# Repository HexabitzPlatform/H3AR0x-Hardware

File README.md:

# H3AR0x-Hardware
Hexabitz Module DIP Adapter Hardware Design

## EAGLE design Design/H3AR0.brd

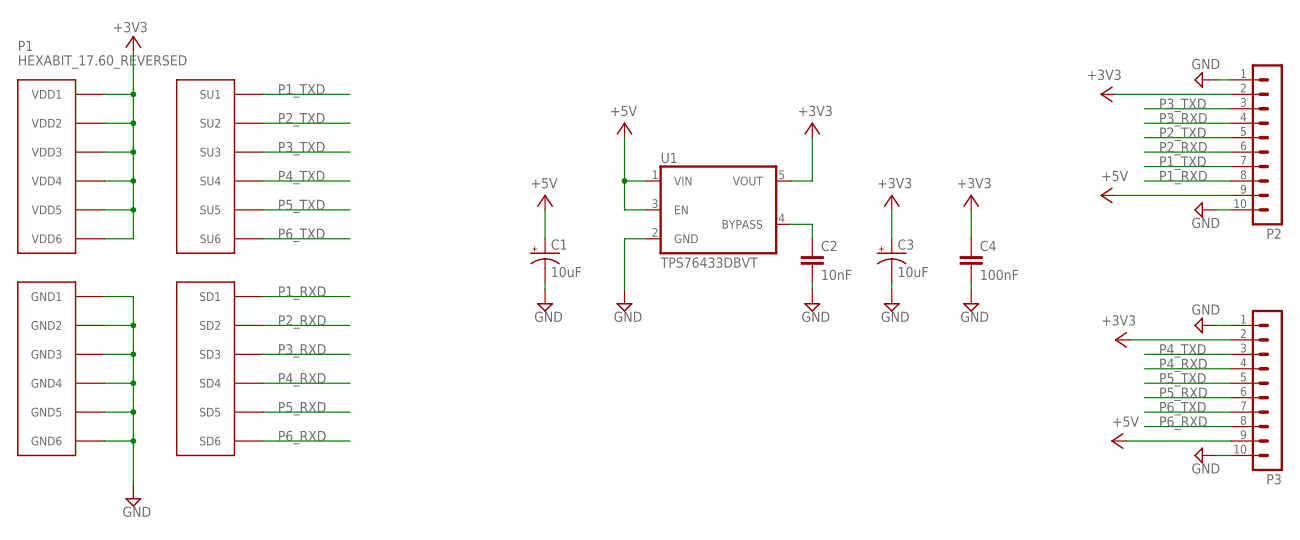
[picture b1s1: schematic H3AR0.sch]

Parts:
C1, C3: 10uF; C-1210-POL; MPN TPSB106K016R0500
C2: 10nF; C-0603; TOLERANCE 10%; VOLTAGE_RATING 50V; MPN C0603C103K5RACTU
C4: 100nF; C-0603; TOLERANCE 10%; VOLTAGE_RATING 10V; MPN C0603C104K8RACTU
P1: HEXABIT_17.60_REVERSED
P2, P3: MA10-1; MPN 61301011121
TRIMBLE-LOGO1: HEXA-LOGO
U1: TPS76433DBVT; SOT25

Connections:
+3V3: C3.1 (+), C4.1, P1.PAD_PU7 (VDD1), P1.PAD_PU8 (VDD2), P1.PAD_PU9 (VDD3), P1.PAD_PU10 (VDD4), P1.PAD_PU11 (VDD5), P1.PAD_PU12 (VDD6), P2.2, P3.2, U1.5 (VOUT)
+5V: C1.1 (+), P2.9, P3.9, U1.1 (VIN), U1.3 (EN)
GND: C1.2 (-), C2.2, C3.2 (-), C4.2, P1.PAD_PD7 (GND1), P1.PAD_PD8 (GND2), P1.PAD_PD9 (GND3), P1.PAD_PD10 (GND4), P1.PAD_PD11 (GND5), P1.PAD_PD12 (GND6), P2.1, P2.10, P3.1, P3.10, U1.2 (GND)
unnamed: C2.1, U1.4 (BYPASS)
P1_RXD: P1.PAD_PD1 (SD1), P2.8
P1_TXD: P1.PAD_PU1 (SU1), P2.7
P2_RXD: P1.PAD_PD2 (SD2), P2.6
P2_TXD: P1.PAD_PU2 (SU2), P2.5
P3_RXD: P1.PAD_PD3 (SD3), P2.4
P3_TXD: P1.PAD_PU3 (SU3), P2.3
P4_RXD: P1.PAD_PD4 (SD4), P3.4
P4_TXD: P1.PAD_PU4 (SU4), P3.3
P5_RXD: P1.PAD_PD5 (SD5), P3.6
P5_TXD: P1.PAD_PU5 (SU5), P3.5
P6_RXD: P1.PAD_PD6 (SD6), P3.8
P6_TXD: P1.PAD_PU6 (SU6), P3.7

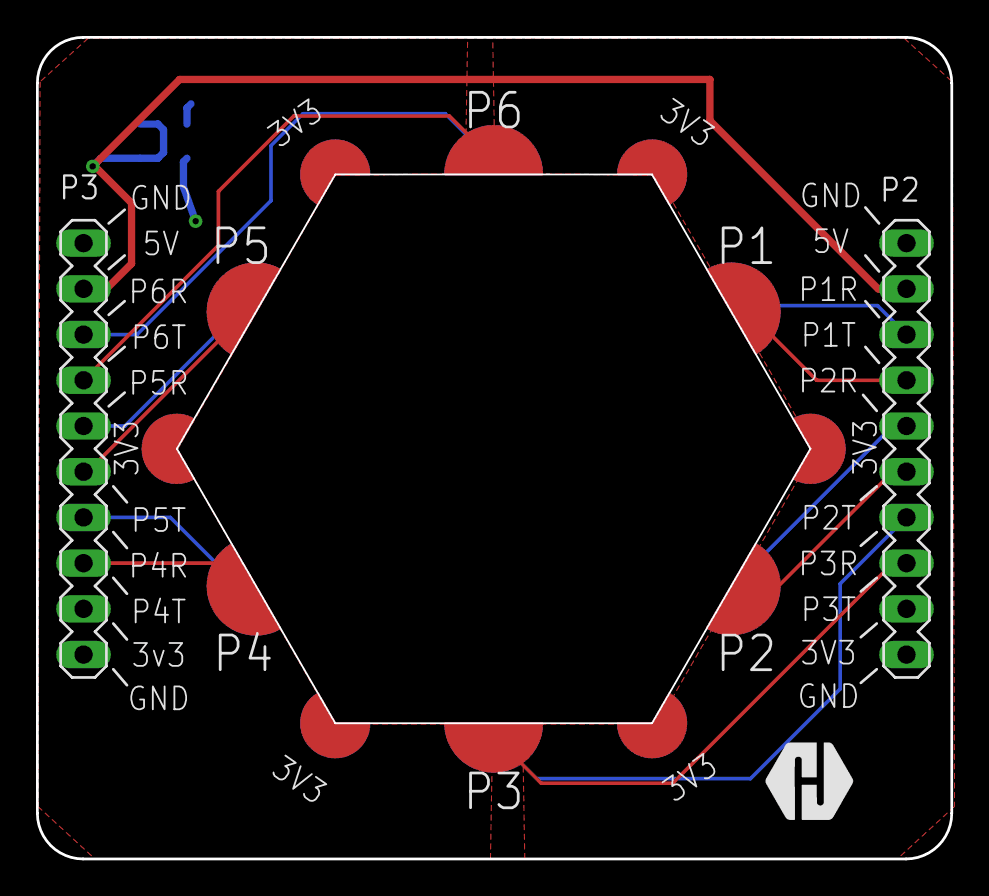
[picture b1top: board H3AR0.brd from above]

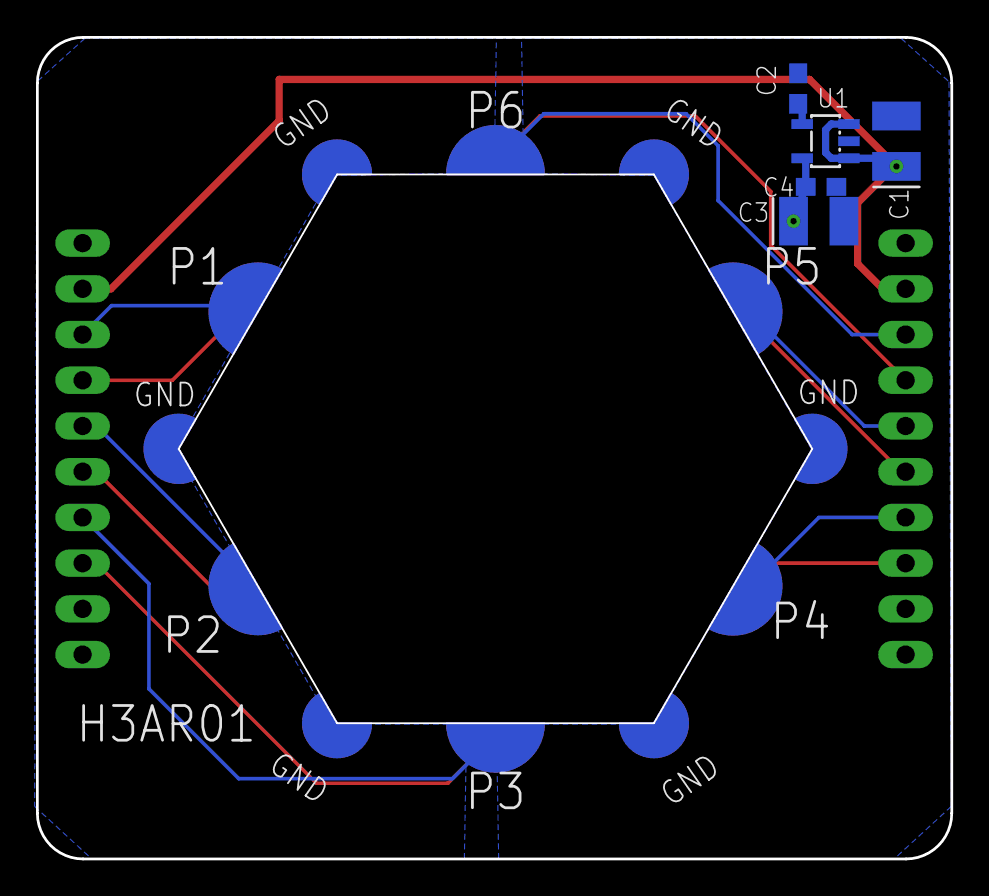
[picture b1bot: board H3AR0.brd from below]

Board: 2 copper layers, 50.8 x 45.6 mm, 9 parts (5 on the bottom side), 16 nets.

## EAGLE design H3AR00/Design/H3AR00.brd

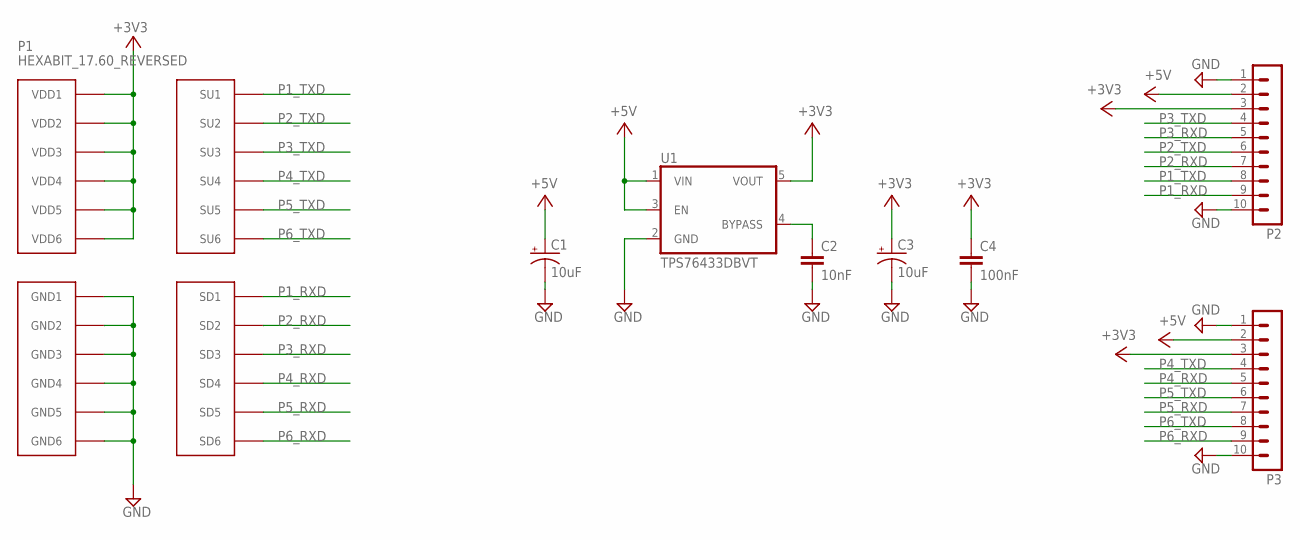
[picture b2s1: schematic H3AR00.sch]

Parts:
C1, C3: 10uF; C-1210-POL; MPN TPSB106K016R0500
C2: 10nF; C-0603; TOLERANCE 10%; VOLTAGE_RATING 50V; MPN C0603C103K5RACTU
C4: 100nF; C-0603; TOLERANCE 10%; VOLTAGE_RATING 10V; MPN C0603C104K8RACTU
P1: HEXABIT_17.60_REVERSED
P2, P3: MA10-1; MPN 61301011121
U1: TPS76433DBVT; SOT25

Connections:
+3V3: C3.1 (+), C4.1, P1.PAD_PU7 (VDD1), P1.PAD_PU8 (VDD2), P1.PAD_PU9 (VDD3), P1.PAD_PU10 (VDD4), P1.PAD_PU11 (VDD5), P1.PAD_PU12 (VDD6), P2.3, P3.3, U1.5 (VOUT)
+5V: C1.1 (+), P2.2, P3.2, U1.1 (VIN), U1.3 (EN)
GND: C1.2 (-), C2.2, C3.2 (-), C4.2, P1.PAD_PD7 (GND1), P1.PAD_PD8 (GND2), P1.PAD_PD9 (GND3), P1.PAD_PD10 (GND4), P1.PAD_PD11 (GND5), P1.PAD_PD12 (GND6), P2.1, P2.10, P3.1, P3.10, U1.2 (GND)
unnamed: C2.1, U1.4 (BYPASS)
P1_RXD: P1.PAD_PD1 (SD1), P2.9
P1_TXD: P1.PAD_PU1 (SU1), P2.8
P2_RXD: P1.PAD_PD2 (SD2), P2.7
P2_TXD: P1.PAD_PU2 (SU2), P2.6
P3_RXD: P1.PAD_PD3 (SD3), P2.5
P3_TXD: P1.PAD_PU3 (SU3), P2.4
P4_RXD: P1.PAD_PD4 (SD4), P3.5
P4_TXD: P1.PAD_PU4 (SU4), P3.4
P5_RXD: P1.PAD_PD5 (SD5), P3.7
P5_TXD: P1.PAD_PU5 (SU5), P3.6
P6_RXD: P1.PAD_PD6 (SD6), P3.9
P6_TXD: P1.PAD_PU6 (SU6), P3.8

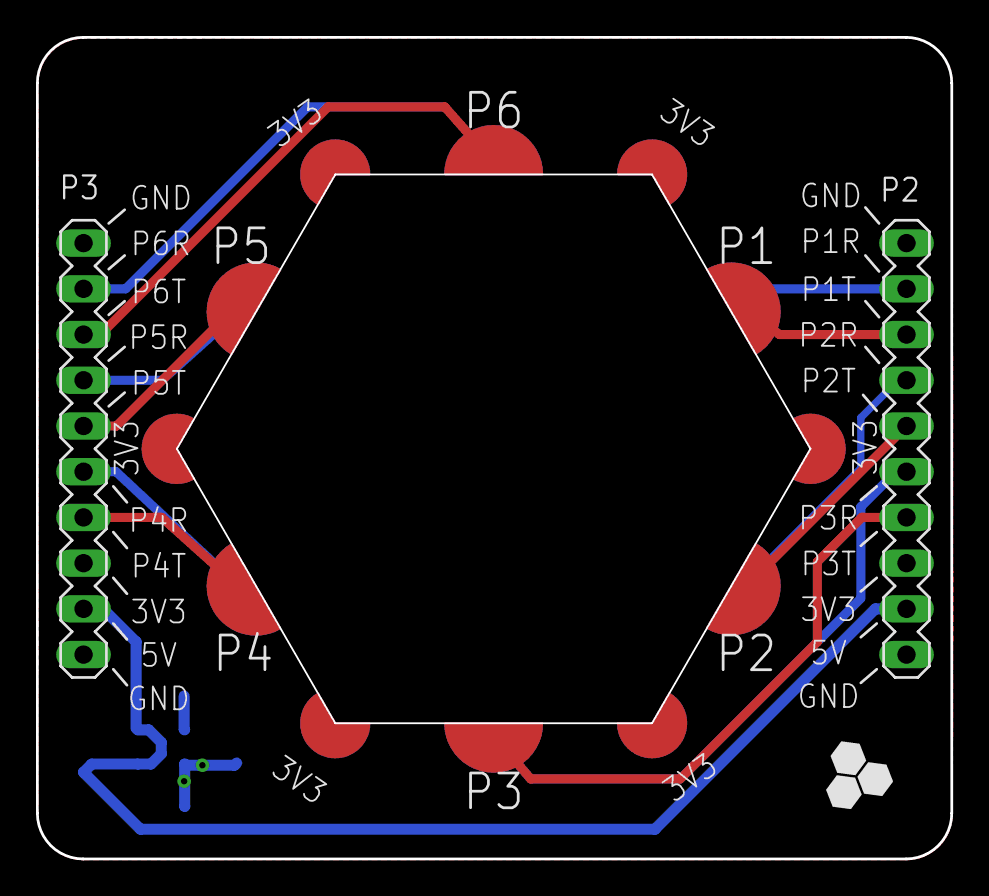
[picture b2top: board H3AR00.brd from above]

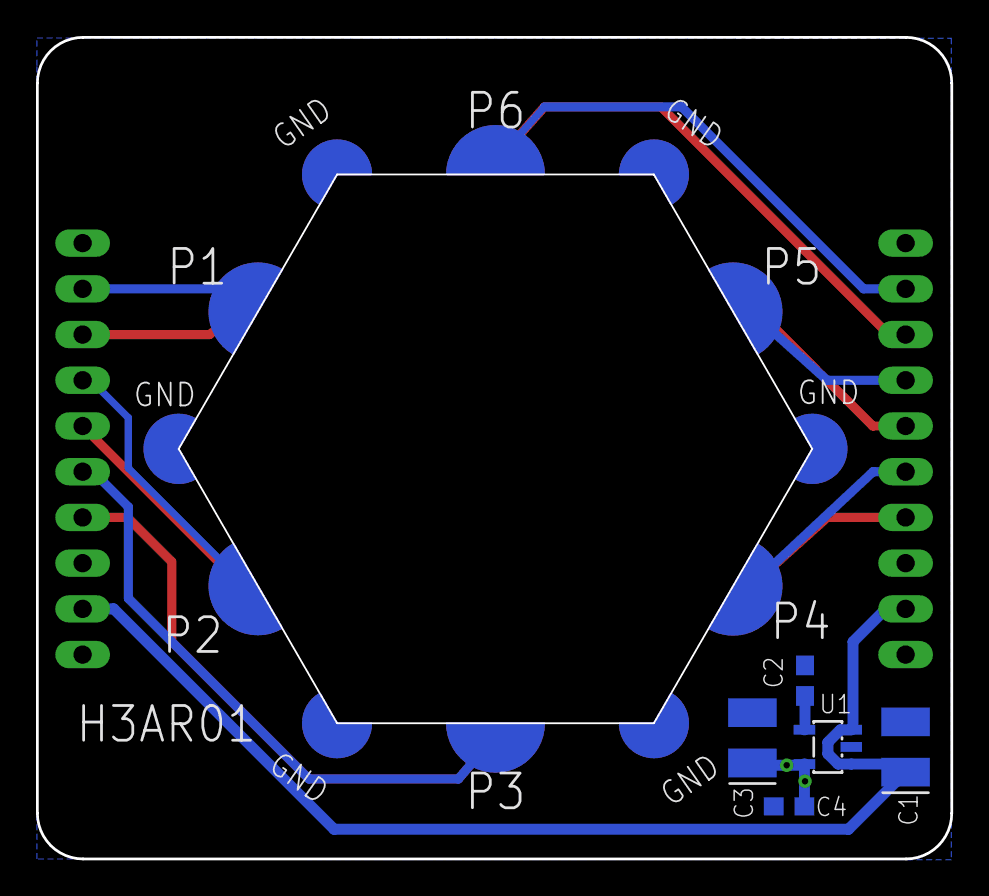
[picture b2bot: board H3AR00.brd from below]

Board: 2 copper layers, 50.8 x 45.6 mm, 8 parts (5 on the bottom side), 16 nets.

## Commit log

2020-01-09 Finish routing, ERC, DRC, add some params
2020-01-09 Adding gerber, pick n place, BOM, schematics, drill
2020-05-12 Reduce module opening from side 18mm to side 17.6mm Revision 1
2024-03-25 -Changnig the 5V pin via the row of pin headers to align with the pin arrangement of the Hex-Cut module.
2024-03-26 Update the logo
